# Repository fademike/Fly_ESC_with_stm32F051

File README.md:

# Fly_ESC_with_stm32F051
ESC for brushless motors.

git clone https://github.com/AlkaMotors/AM32-MultiRotor-ESC-firmware
git current project
cd AM32-MultiRotor-ESC-firmware
git apply am32ref_f051.patch (from current project)
May be to change make/tools: GCC_REQUIRED_VERSION ?= 10.3.1
make f051
STM32_Programmer_CLI -c port=swd -w ./obj/AM32_AM32REF_F051_2.00.bin 0x08000000 –verify -hardRst

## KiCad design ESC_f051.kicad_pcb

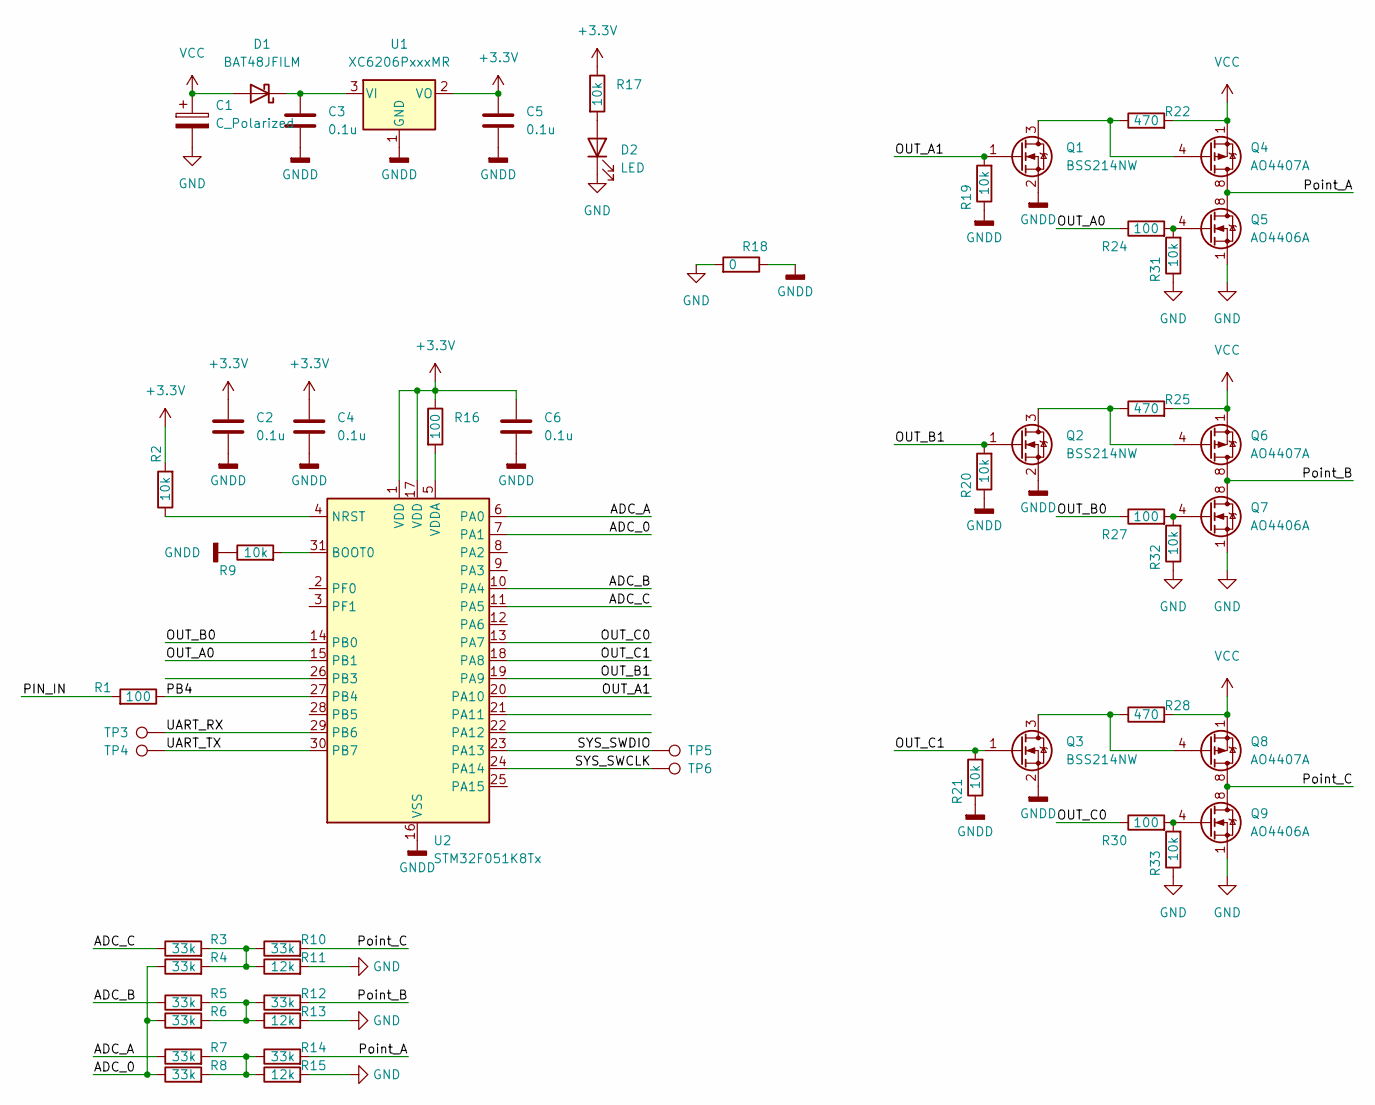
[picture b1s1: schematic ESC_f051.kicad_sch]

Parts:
C1: C_Polarized; CP_EIA-6032-28_Kemet-C
C2, C3, C4, C5, C6: 0.1u; C_0402_1005Metric
D1: BAT48JFILM; D_SOD-323
D2: LED; LED_0805_2012Metric
Q1, Q2, Q3: BSS214NW; SOT-323_SC-70
Q4, Q6, Q8: AO4407A; SOIC-8_3.9x4.9mm_P1.27mm
Q5, Q7, Q9: AO4406A; SOIC-8_3.9x4.9mm_P1.27mm
R1, R16, R24, R27, R30: 100; R_0402_1005Metric
R2, R9, R17, R19, R20, R21, R31, R32, R33: 10k; R_0402_1005Metric
R3, R4, R5, R6, R7, R8, R10, R12, R14: 33k; R_0402_1005Metric
R11, R13, R15: 12k; R_0402_1005Metric
R18: 0; R_0402_1005Metric
R22, R25, R28: 470; R_0402_1005Metric
TP3, TP4, TP5, TP6: TestPoint; TestPoint_Pad_D1.0mm
U1: XC6206PxxxMR; SOT-23
U2: STM32F051K8Tx; LQFP-32_7x7mm_P0.8mm

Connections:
+3.3V: C2.2, C4.2, C5.1, C6.2, R2.2, R16.1, R17.1, U1.2 (VO), U2.1 (VDD), U2.17 (VDD)
/ADC_0: R4.1, R6.1, R8.1, U2.7 (PA1)
/ADC_A: R7.1, U2.6 (PA0)
/ADC_B: R5.1, U2.10 (PA4)
/ADC_C: R3.1, U2.11 (PA5)
/OUT_A0: R24.1, U2.15 (PB1)
/OUT_A1: Q1.1 (G), R19.2, U2.20 (PA10)
/OUT_B0: R27.1, U2.14 (PB0)
/OUT_B1: Q2.1 (G), R20.2, U2.19 (PA9)
/OUT_C0: R30.1, U2.13 (PA7)
/OUT_C1: Q3.1 (G), R21.2, U2.18 (PA8)
/PB4: R1.1, U2.27 (PB4)
/PIN_IN: R1.2
/Point_A: Q4.5 (D), Q4.6 (D), Q4.7 (D), Q4.8 (D), Q5.5 (D), Q5.6 (D), Q5.7 (D), Q5.8 (D), R14.2
/Point_B: Q6.5 (D), Q6.6 (D), Q6.7 (D), Q6.8 (D), Q7.5 (D), Q7.6 (D), Q7.7 (D), Q7.8 (D), R12.2
/Point_C: Q8.5 (D), Q8.6 (D), Q8.7 (D), Q8.8 (D), Q9.5 (D), Q9.6 (D), Q9.7 (D), Q9.8 (D), R10.2
/SYS_SWCLK: TP6.1, U2.24 (PA14)
/SYS_SWDIO: TP5.1, U2.23 (PA13)
/UART_RX: TP3.1, U2.29 (PB6)
/UART_TX: TP4.1, U2.30 (PB7)
GND: C1.2, D2.1 (K), Q5.1 (S), Q5.2 (S), Q5.3 (S), Q7.1 (S), Q7.2 (S), Q7.3 (S), Q9.1 (S), Q9.2 (S), Q9.3 (S), R11.2, R13.2, R15.2, R18.2, R31.1, R32.1, R33.1
GNDD: C2.1, C3.2, C4.1, C5.2, C6.1, Q1.2 (S), Q2.2 (S), Q3.2 (S), R9.1, R18.1, R19.1, R20.1, R21.1, U1.1 (GND), U2.16 (VSS), U2.32 (VSS)
unnamed: C3.1, D1.1 (K), U1.3 (VI)
unnamed: D2.2 (A), R17.2
unnamed: Q1.3 (D), Q4.4 (G), R22.1
unnamed: Q2.3 (D), Q6.4 (G), R25.1
unnamed: Q3.3 (D), Q8.4 (G), R28.1
unnamed: Q5.4 (G), R24.2, R31.2
unnamed: Q7.4 (G), R27.2, R32.2
unnamed: Q9.4 (G), R30.2, R33.2
unnamed: R3.2, R4.2, R10.1, R11.1
unnamed: R5.2, R6.2, R12.1, R13.1
unnamed: R7.2, R8.2, R14.1, R15.1
unnamed: R9.2, U2.31 (BOOT0)
unnamed: R2.1, U2.4 (NRST)
unnamed: R16.2, U2.5 (VDDA)
VCC: C1.1, D1.2 (A), Q4.1 (S), Q4.2 (S), Q4.3 (S), Q6.1 (S), Q6.2 (S), Q6.3 (S), Q8.1 (S), Q8.2 (S), Q8.3 (S), R22.2, R25.2, R28.2

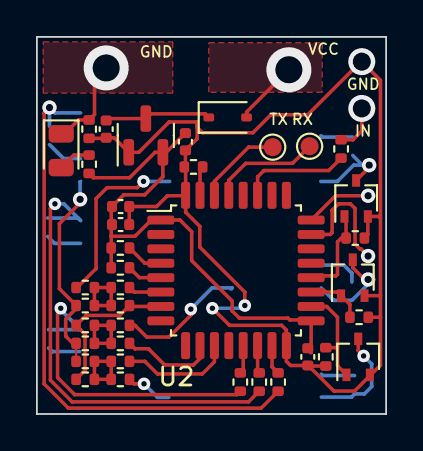
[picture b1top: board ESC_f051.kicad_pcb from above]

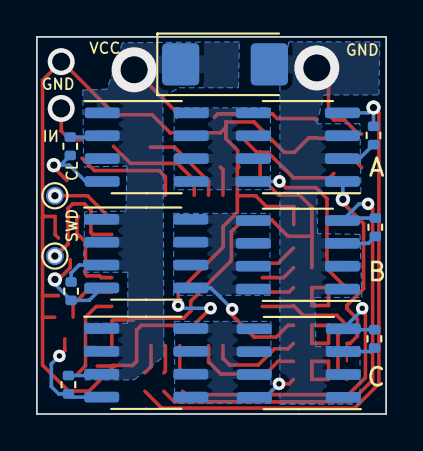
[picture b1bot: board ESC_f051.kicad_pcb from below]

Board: 2 copper layers, 19.4 x 20.9 mm, 53 parts (15 on the bottom side), 36 nets.

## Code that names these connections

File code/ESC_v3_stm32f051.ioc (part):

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Mcu.Name=STM32F051K8Tx
Mcu.Package=LQFP32
Mcu.UserName=STM32F051K8Tx
PA10.GPIOParameters=GPIO_Speed,GPIO_Label
PA10.GPIO_Label=OUT_C1
PA10.GPIO_Speed=GPIO_SPEED_FREQ_HIGH
PA10.Signal=GPIO_Output
PA13.Mode=Serial_Wire
PA13.Signal=SYS_SWDIO
PA14.Mode=Serial_Wire
PA14.Signal=SYS_SWCLK
PA15.GPIOParameters=GPIO_Speed,GPIO_Label
PA15.GPIO_Label=OUT_A0
PA15.GPIO_Speed=GPIO_SPEED_FREQ_HIGH
PA15.Signal=GPIO_Output
PA3.Mode=INP
PA3.Signal=COMP2_INP
PA4.Mode=INM
PA4.Signal=COMP2_INM
PA8.GPIOParameters=GPIO_Speed,GPIO_Label
PA8.GPIO_Label=OUT_A1
PA8.GPIO_Speed=GPIO_SPEED_FREQ_HIGH
PA8.Signal=GPIO_Output
PA9.GPIOParameters=GPIO_Speed,GPIO_Label
PA9.GPIO_Label=OUT_B1
PA9.GPIO_Speed=GPIO_SPEED_FREQ_HIGH
PA9.Signal=GPIO_Output
PB3.GPIOParameters=GPIO_Speed,GPIO_Label
PB3.GPIO_Label=OUT_B0
PB3.GPIO_Speed=GPIO_SPEED_FREQ_HIGH
PB3.Signal=GPIO_Output
PB4.GPIOParameters=GPIO_Speed,GPIO_Label
PB4.GPIO_Label=OUT_C0
PB4.GPIO_Speed=GPIO_SPEED_FREQ_HIGH
PB4.Signal=GPIO_Output
PB5.GPIOParameters=GPIO_PuPd,GPIO_Label,GPIO_ModeDefaultEXTI
PB5.GPIO_Label=TEST_IN
PB5.GPIO_ModeDefaultEXTI=GPIO_MODE_IT_RISING_FALLING
PB5.GPIO_PuPd=GPIO_PULLUP
PB5.Signal=GPXTI5
PB6.Mode=Half_duplex(single_wire_mode)
PB6.Signal=USART1_TX
PB7.GPIOParameters=GPIO_Speed,GPIO_Label,GPIO_FM7
PB7.GPIO_FM7=SYSCFG_CFGR1_I2C_FMP_PB7
PB7.GPIO_Label=TEST_OUT
PB7.GPIO_Speed=GPIO_SPEED_FREQ_HIGH
PB7.Signal=GPIO_Output
RCC.SYSCLKFreq_VALUE=48000000
RCC.SYSCLKSource=RCC_SYSCLKSOURCE_PLLCLK
board=ESC_v3_stm32f051

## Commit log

2024-04-30 remaked to kicad
2024-08-24 reduced the size
